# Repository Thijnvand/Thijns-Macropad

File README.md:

# hackclub
I have made a hackpad using Fusion and KiCad. I have made a simple construction with 4 keys, 7 LEDs, and an OLED screen. I put the LEDs next to the switches so they can tell which switch has been pressed, and I put three LEDs at the bottom. Also, above the switches is an OLED screen which can display various things. The bottom part of the case is just a simple holder for the PCB with holes in it for heat-set inserts. I had never used KiCad before in my life, so with a few YouTube videos and various hours of trial and error, I made my PCB. I had experience with CAD software, but not with Fusion, but that part went relatively well.

Overall, I like my creation and gained some skills from using KiCad and Fusion!
This is my hackpad: 
PCB and schematic:

CAD model:

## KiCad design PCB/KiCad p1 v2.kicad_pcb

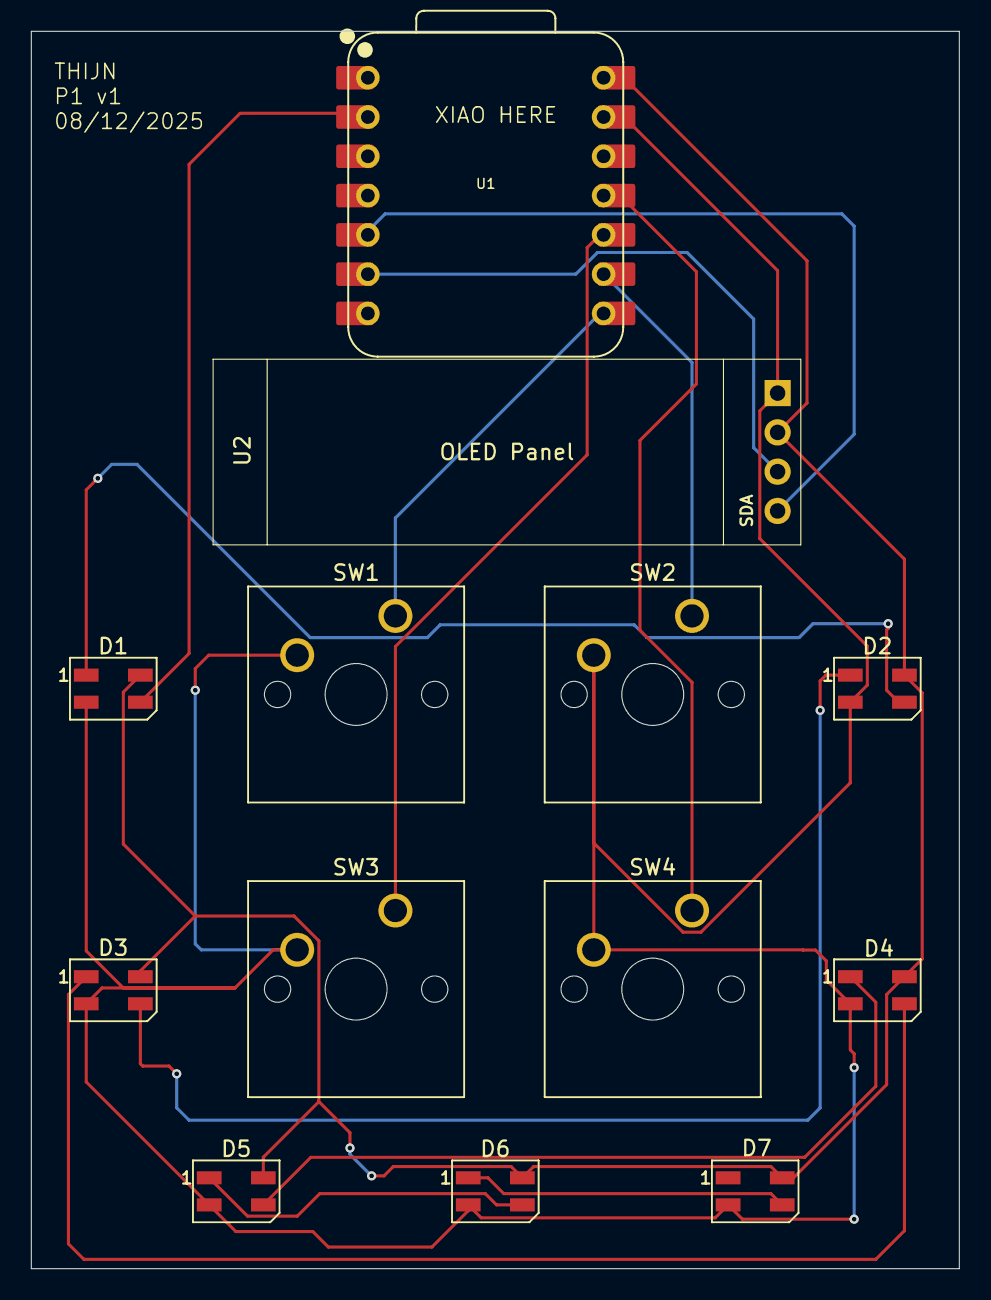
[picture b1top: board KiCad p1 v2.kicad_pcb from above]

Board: 2 copper layers, 60.0 x 80.0 mm, 13 parts (0 on the bottom side), 15 nets.

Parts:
D1, D2, D3, D4, D5, D6, D7: SK6812MINI; LED_SK6812MINI_PLCC4_3.5x3.5mm_P1.75mm
SW1, SW2, SW3, SW4: SW_Push; SW_Cherry_MX_1.00u_PCB
U1: XIAO-RP2040-DIP
U2: SSD1306-0.91-OLED-4pin-128x32

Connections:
+5V: D1.4 (VDD), D2.4 (VDD), D3.4 (VDD), D4.4 (VDD), D5.4 (VDD), D6.4 (VDD), D7.4 (VDD), U1.14 (VBUS), U2.2 (VCC)
GND: D1.2 (VSS), D2.2 (VSS), D3.2 (VSS), D4.2 (VSS), D5.2 (VSS), D6.2 (VSS), D7.2 (VSS), SW1.2, SW2.2, SW3.2, SW4.2, U1.13 (GND), U2.1 (GND)
unnamed: D1.3 (DIN), U1.2 (GPIO27/ADC1/A1)
unnamed: D1.1 (DOUT), D2.3 (DIN)
unnamed: D2.1 (DOUT), D3.3 (DIN)
unnamed: D3.1 (DOUT), D4.3 (DIN)
unnamed: D4.1 (DOUT), D5.3 (DIN)
unnamed: D5.1 (DOUT), D6.3 (DIN)
unnamed: D6.1 (DOUT), D7.3 (DIN)
unnamed: SW1.1, U1.8 (GPIO1/RX)
unnamed: SW2.1, U1.9 (GPIO2/SCK)
unnamed: SW4.1, U1.11 (GPIO3/MOSI)
unnamed: SW3.1, U1.10 (GPIO4/MISO)
unnamed: U1.5 (GPIO6/SDA), U2.4 (SDA)
unnamed: U1.6 (GPIO7/SCL), U2.3 (SCL)

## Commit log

2025-12-10 Create CAD
2025-12-10 Update CAD
2025-12-10 Update BOM
